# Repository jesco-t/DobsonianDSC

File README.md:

# Digital Setting Circles for a Manual Telescope Mount.

Design and code based on this GitHub project https://github.com/vlaate/DobsonianDSC. Code is converted to PlatformIO and a few bugs fixed (mostly due to newer dependencies having deprecated some usage patterns). A discussion thread on CloudyNights can be found here https://www.cloudynights.com/topic/589521-37-dobsonian-dsc-for-diy-makers/.

The PCB is designed for the NodeMCU DevKit C module. It is my own design.

The CAD files for the 10" Meade Lightbride are my own original design.
## PCB

The PCB is designed for the NodeMCU DevKit C. It uses 12V DC as power supply which should be readily available. It uses a 100uF input capacitor and 5V DC/DC converter to supply a stable voltage to the encoders. The ESP32 is not 5V tolerant on its GPIO pins which requires the 4-channel level shifter between NodeMCU and the encoders. 

The connectors to the encoders are JST-XH, which require a special crimp tool and some practice. The tool is extra 30€ or so but it’s well worth it in my opinion. The pinning is `+5V, GND, A, B, Shield/GND`.

The case for the board is a marginal fit because the screw holes are off by a few hundred micron. Apologies. If you want to fix it, I recommend updating the board layout in KiCAD and not the case in FreeCAD. It’s the board that has the odd measurements.

The Gerber files in the repository are suitable for JLPCB which I can highl recommend. A set of 5 boards cost me <10€.

## Software

The software needs to be compiled and uploaded with PlatformIO. Like the ArduinoIDE it's free. You need to install VSCode and the the PlatformIO extension. There are no changes needed to upload.
## Modifications on the 10" Meade Lightbridge

I use a gear driven mechanism for the encoder train. I decided against belts because the altitude axis needs to be easily to dismantle. The azimuth axis uses the same gear ratio. 

## Altitude Axis

The altitude gear is attached in three pieces: a mounting ring is glued onto the metal trunnion. The mounting ring has 4x M3 heat inserts. Then a spacer ring and the gear ring is threaded on with M3 screws.

The encoder is screwed into its mount. The encoder gear is loosely slid over the encoder and the proper spacing to the axis gear is determined. The gears should mesh well with a bit but not too much play. Mark the position and screw the encoder mount onto the base.

The axis gear has 155 teeth and the Encoder gear has 62. With 2400 pulses on the quadrature encoder this makes for 6000 steps across a 360° totation of the axis.

## Azimuth Axis

The azimuth gear is mounted in the azimuth tension knob. It's held onto the knob with four M3 screws. The setup is the same as the altitude gear: mounting ring, spacer and then the actual gear. Here, the spacer and gear are attached with individual screws.

The encoder is attached in a similar fashion than the altitude encoder. The gear itself is mounted reverse compared to the altitude axis. For the AZ gear, use the same STL file as-is for ALT gear on the encoder. Use your slicer to remove the upper 5mm of the gear so that the height of the gear mesh is correct.

The axis gear has 155 teeth and the Encoder gear has 62. With 2400 pulses on the quadrature encoder this makes for 6000 steps across a 360° totation of the axis.

## Bill-of-Materials

| Module  | Item                            | Pieces | Description                |
| ------- | ------------------------------- | ------ | -------------------------- |
| PCB     | NodeMCU DevKit C                | 1      |                            |
| PCB     | OKI-SR78-5/1.5-W36-C            | 1      | 5V DC/DC converter         |
| PCB     | Capacitor (100uF/>25V)          | 1      | 47uF is also ok            |
| PCB     | 4-Channel Level Shifter 5V~3.3V | 1      | needs VC/GND in the middle |
| PCB     | JST-XH 2.54 Plug & Socket       | 2      | need crimp tool also       |
| PCB     | 5.5x2.1 DC Socket               | 1      |                            |
| Encoder | 600 steps A/B Encoder           | 2      |                            |
| Misc    | M3 Screw Set                    | 1      |                            |
| Misc    | M3 Heat Insets                  | 20     |                            |
| Misc    | 3x20 Wood Screws                | 8      |                            |

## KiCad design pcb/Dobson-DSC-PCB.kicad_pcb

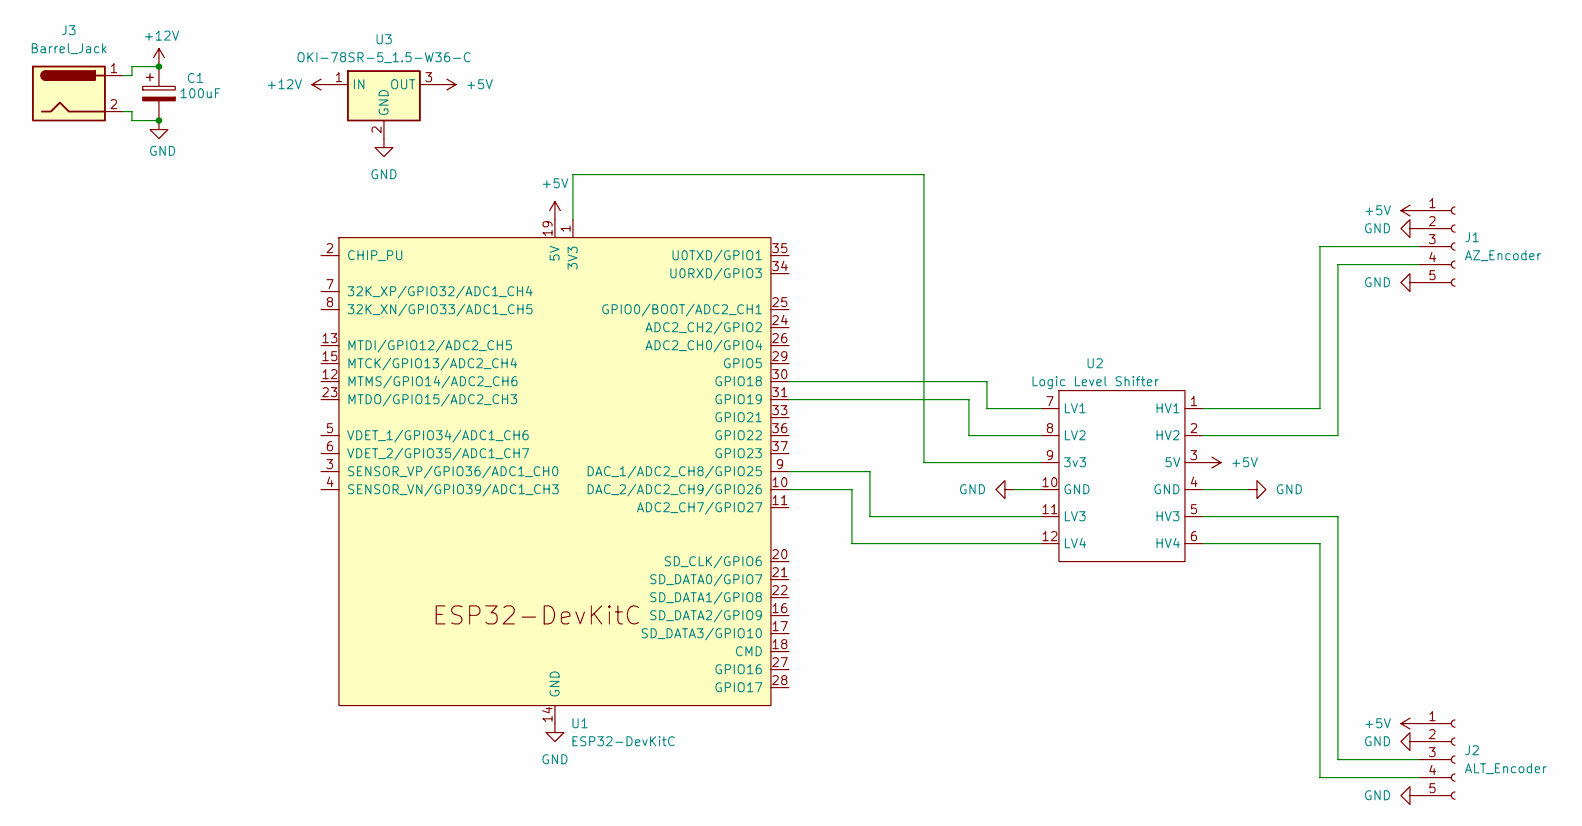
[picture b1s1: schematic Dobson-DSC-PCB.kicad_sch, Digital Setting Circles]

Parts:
C1: C_Polarized; CP_Radial_D5.0mm_P2.50mm
J1: AZ_Encoder; JST_XH_B5B-XH-AM_1x05_P2.50mm_Vertical
J2: ALT_Encoder; JST_XH_B5B-XH-AM_1x05_P2.50mm_Vertical
J3: Barrel_Jack; BarrelJack_Horizontal
U1: ESP32-DevKitC
U2: Logic Level Shifter; Level-Shifter 4
U3: OKI-78SR-5_1.5-W36-C; Converter_DCDC_Murata_OKI-78SR_Vertical

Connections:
+5V: J1.1, J2.1, U1.19 (5V), U2.3 (5V), U3.3 (OUT)
+12V: C1.1, J3.1, U3.1 (IN)
GND: C1.2, J1.2, J1.5, J2.2, J2.5, J3.2, U1.14 (GND), U1.32 (GND), U1.38 (GND), U2.4 (GND), U2.10 (GND), U3.2 (GND)
unnamed: J1.3, U2.1 (HV1)
unnamed: J1.4, U2.2 (HV2)
unnamed: J2.3, U2.5 (HV3)
unnamed: J2.4, U2.6 (HV4)
unnamed: U1.1 (3V3), U2.9 (3v3)
unnamed: U1.9 (DAC_1/ADC2_CH8/GPIO25), U2.11 (LV3)
unnamed: U1.10 (DAC_2/ADC2_CH9/GPIO26), U2.12 (LV4)
unnamed: U1.30 (GPIO18), U2.7 (LV1)
unnamed: U1.31 (GPIO19), U2.8 (LV2)

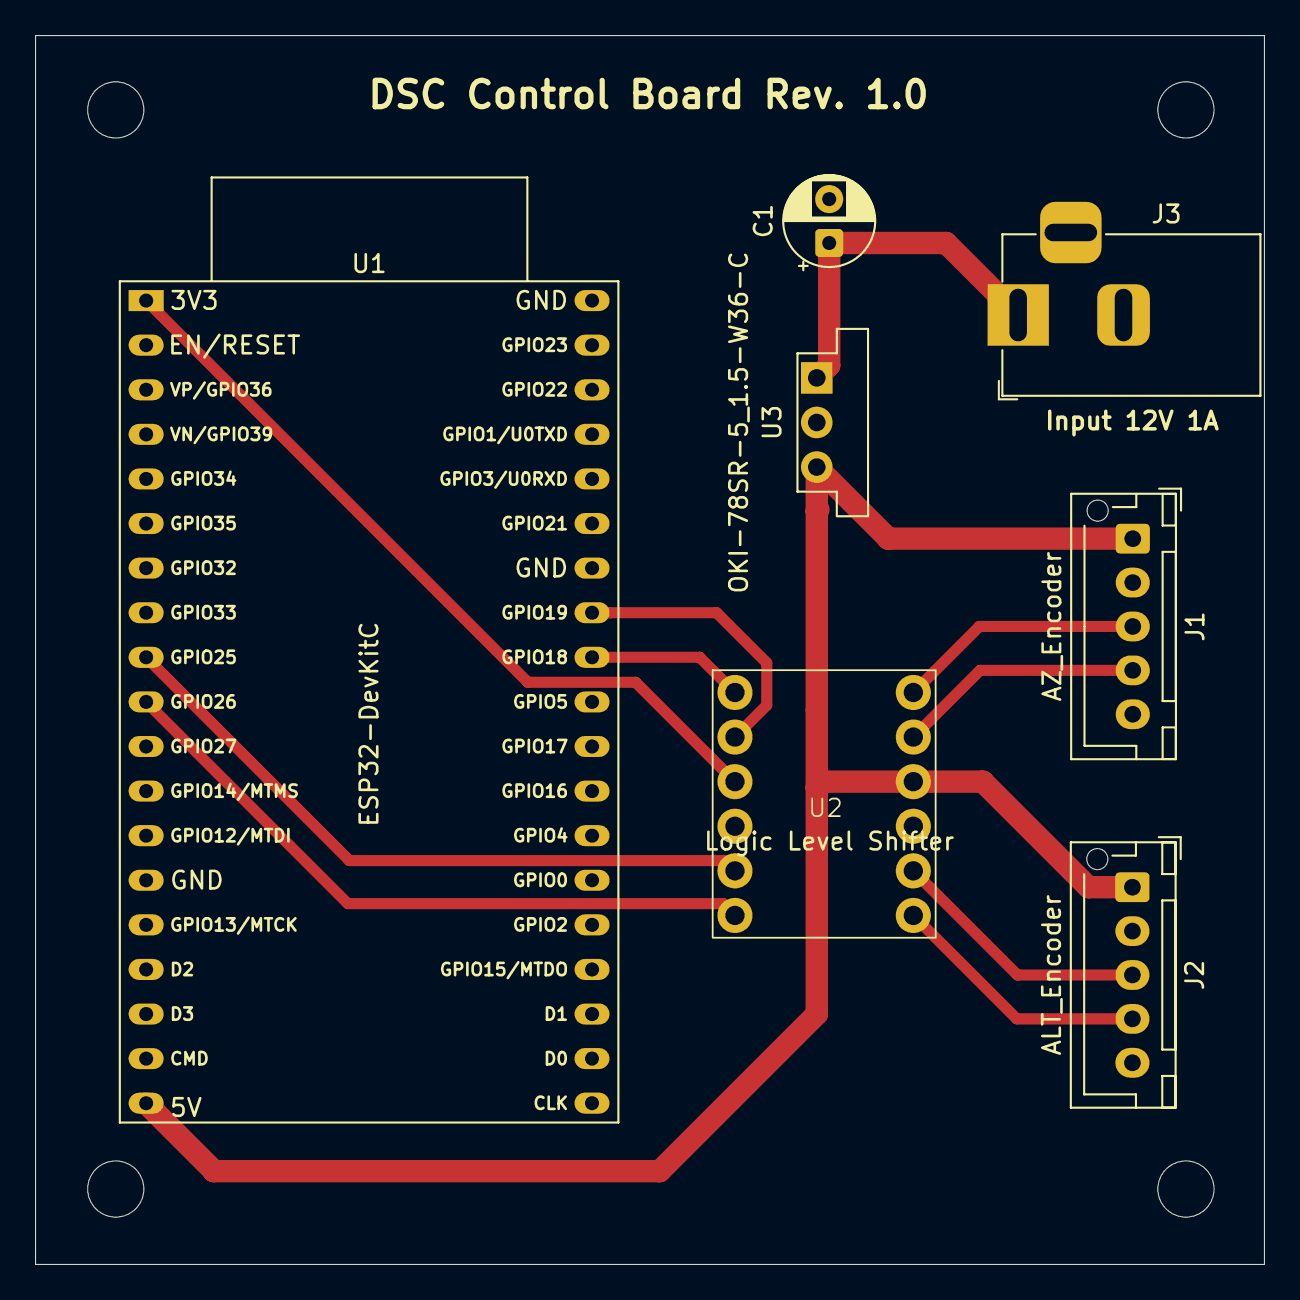
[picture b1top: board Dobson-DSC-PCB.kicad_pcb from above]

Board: 2 copper layers, 70.0 x 70.0 mm, 7 parts (0 on the bottom side), 12 nets.

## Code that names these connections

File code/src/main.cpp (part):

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
    ESP32 pinout:
     IMPORTANT: Only encoders with NPN Open collector outputs can be connected directly to the pins of the ESP32. Other encoders might require level shifters.
     AZ_Encoder_A = GPIO18 = D18  (or change it in the #define code below)
     AZ_Encoder_B = GPIO19 = D19  (or change it in the #define code below)
     ALT_Encoder_A = GPIO25 = D25 (or change it in the #define code below)
     ALT_Encoder_B = GPIO26 = D26 (or change it in the #define code below)
     VIN = Encoder VCC (and if you don't use a USB power bank, this would also connect to your 5V power source)
     GND = Encoder GND
*/
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
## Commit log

2025-07-14 Remove old project files due to PlatformIO port
2025-07-14 add final code from local server
2025-07-14 add gear ratio and steps per revolution for both axis
2025-07-14 increase PCB case bottom
    3x20 wood screw would punch through the base board otherwise
2025-08-12 add encoder-pinout description

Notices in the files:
code/src/main.cpp:
Copyright (c) 2017-2021 Vladimir Atehortúa. All rights reserved.
This program is free software: you can redistribute it and/or modify
it under the terms of the version 3 GNU General Public License as
published by the Free Software Foundation.
